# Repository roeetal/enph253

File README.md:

# enph253
## Robot competition

### Links
* Main source-code folder: https://github.com/roeetal/enph253/tree/master/Software/STM32/brain
* Google Slides for technical presentation: 
  https://docs.google.com/presentation/d/15P2V7RuZFssEo_z1w1n5baqb6ON2kBNIlDU9cCNbAWw/edit?usp=sharing
* Report / website:
https://axel-jacobsen.github.io/ENPHRobot/

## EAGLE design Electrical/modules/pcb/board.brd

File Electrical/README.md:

# Electrical

## Libraries

Create individual components that you cannot find or import from somewhere else.

## Design Blocks

Multiple compoenents connected together to form a single module, or design block. These get imported into the schematic.

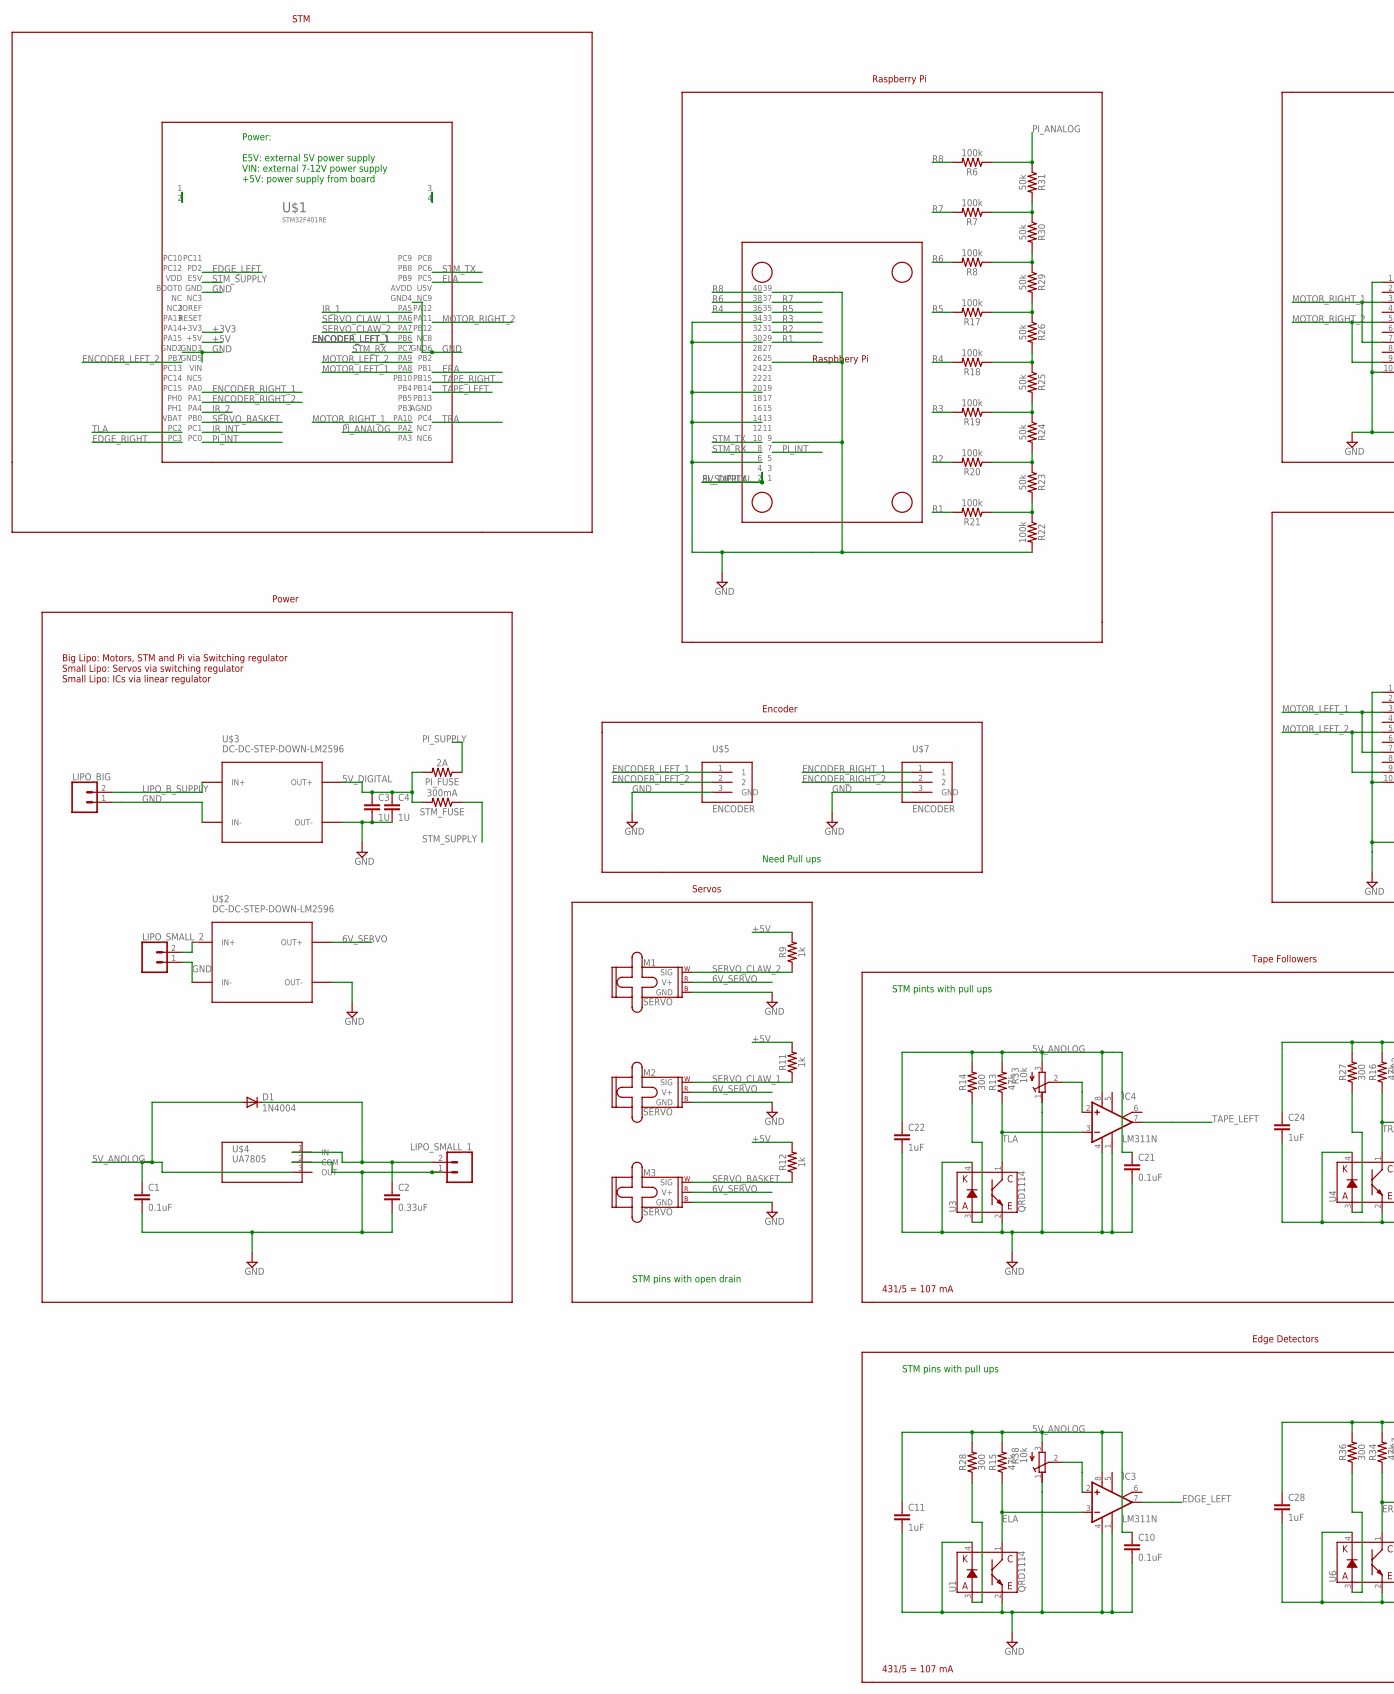
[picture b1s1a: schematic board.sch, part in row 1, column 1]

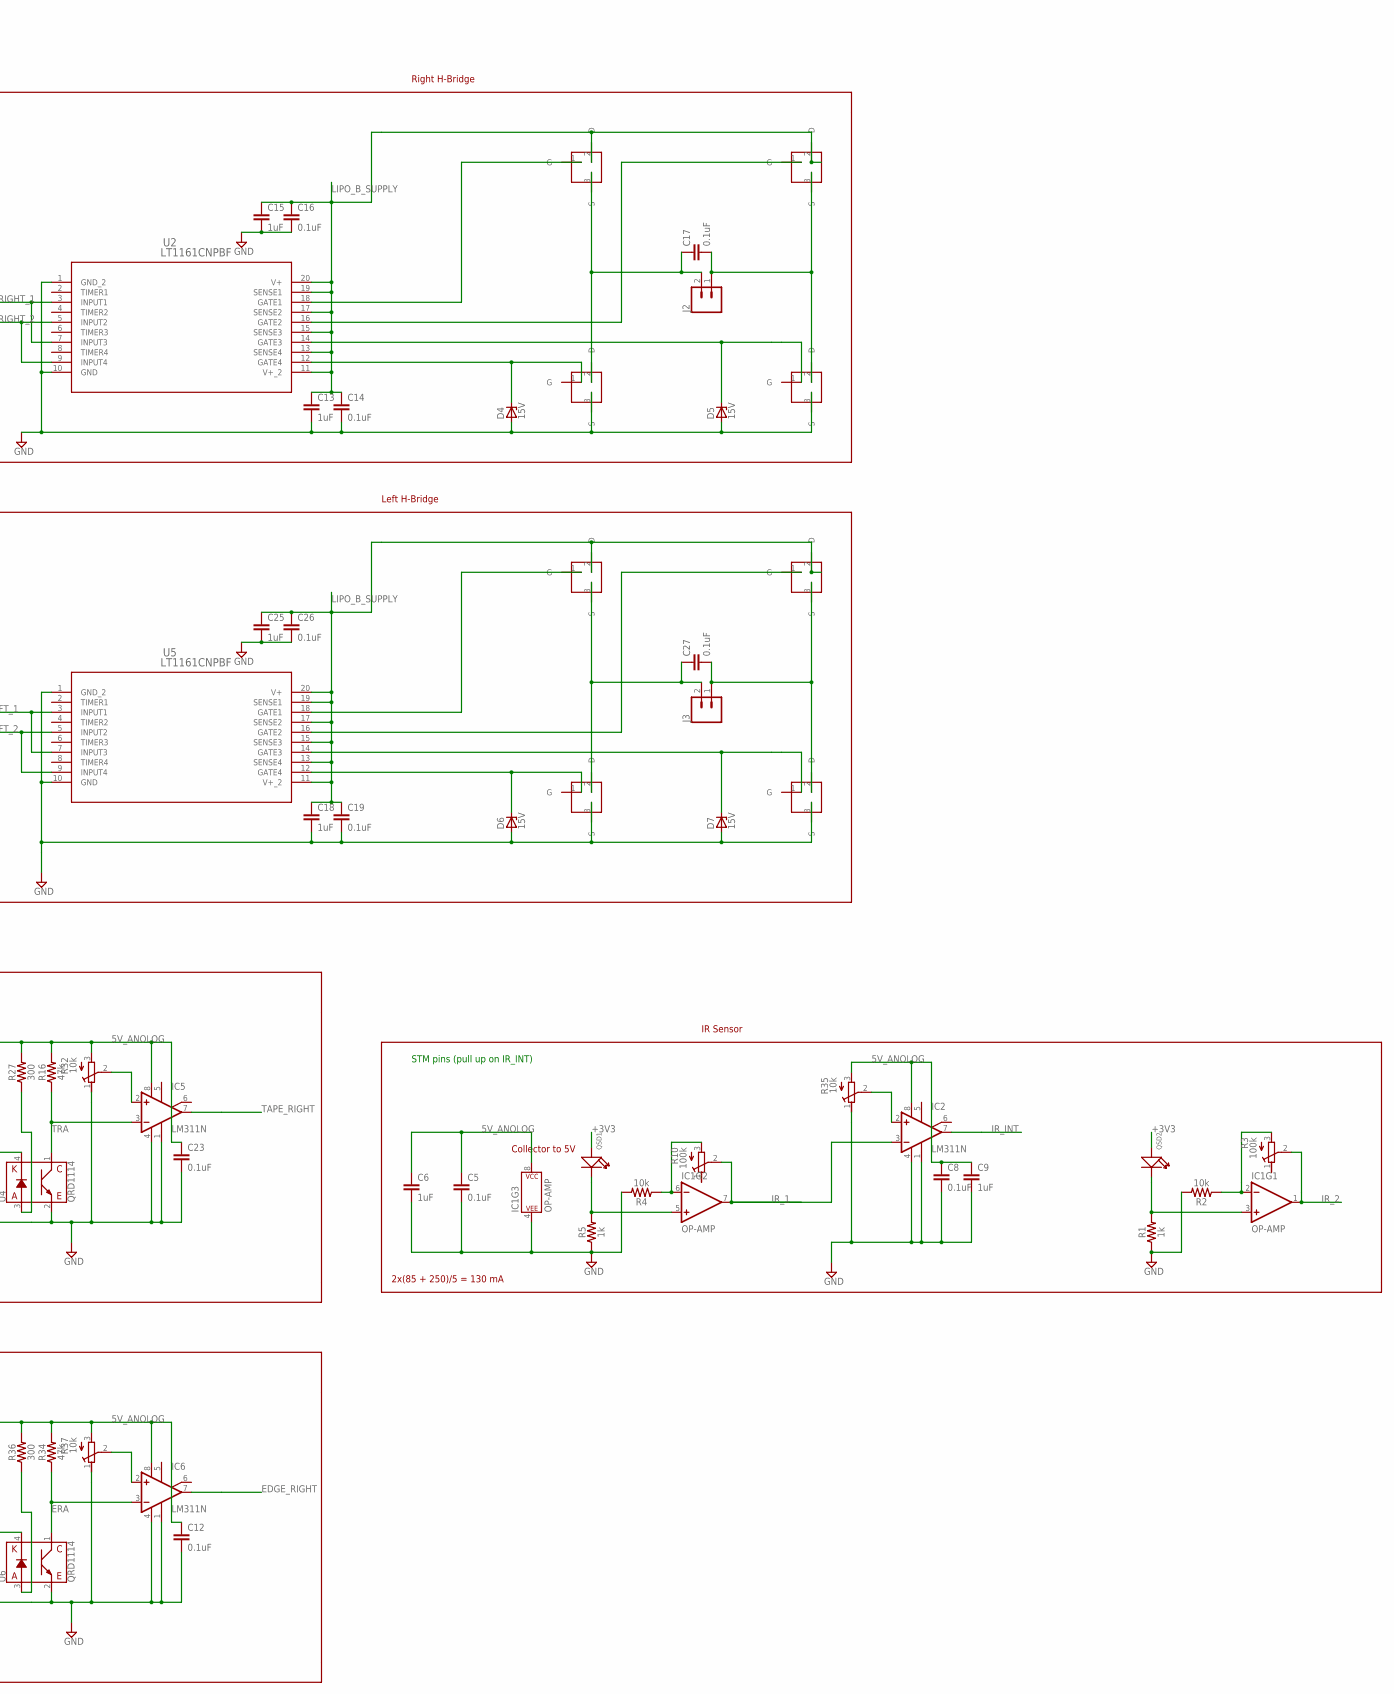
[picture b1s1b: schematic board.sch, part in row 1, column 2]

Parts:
C1, C5, C8, C10, C12, C14, C16, C17, C19, C21, C23, C26, C27: 0.1uF; CAP-PTH-SMALL-KIT
C2: 0.33uF; CAP-PTH-SMALL-KIT
C3, C4: 1U; C5B5
C6, C9, C11, C13, C15, C18, C22, C24, C25, C28: 1uF; CAP-PTH-SMALL-KIT
D1: 1N4004; DO41-10
D4, D5, D6, D7: 15V; DO41Z10
IC1: OP-AMP; DIP08
IC2, IC3, IC4, IC5, IC6: LM311N; DIL08
J2, J3: CONN_02; 1X02
LIPO_BIG: CONN_02; 1X02
LIPO_SMALL_1, LIPO_SMALL_2: CONN_02; 1X02
M1, M2, M3: SERVO; 1X03
PI_FUSE: 2A; AXIAL-0.3
QSD1, QSD2: DIP-LED-GREEN-GREEN(2P-D5MM); LED2-2.54-D5.0MM
R1, R5, R9, R11, R12: 1k; AXIAL-0.3
R2, R4: 10k; AXIAL-0.3
R3, R10: 100k; RTRIMT93YA
R6, R7, R8, R17, R18, R19, R20, R21, R22: 100k; AXIAL-0.3
R13, R15, R16, R34: 47k; AXIAL-0.3
R14, R27, R28, R36: 300; AXIAL-0.3
R23, R24, R25, R26, R29, R30, R31: 50k; AXIAL-0.3
R32, R33, R35, R37, R38: 10k; RTRIMT93YA
STM_FUSE: 300mA; AXIAL-0.3
U1, U3, U4, U6: QRD1114
U2, U5: LT1161CNPBF; PDIP-20_N
U$1: STM32F401RE; STM32
U$2, U$3: DC-DC-STEP-DOWN-LM2596
U$4: UA7805; TO-220AB
U$5, U$7: ENCODER; TO-220AB
U$6: RPI3; PI
U$11, U$12, U$13, U$14, U$15, U$16, U$17, U$18: HUF75321; TO-220AB

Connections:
5V_ANOLOG: C1.1, C5.1, C6.1, C8.1, C9.1, C10.1, C11.1, C12.1, C21.1, C22.1, C23.1, C24.1, C28.1, D1.A, IC1.8 (P$V+), IC2.8 (V+), IC3.8 (V+), IC4.8 (V+), IC5.8 (V+), IC6.8 (V+), R13.P$2 (2), R14.P$2 (2), R15.P$2 (2), R16.P$2 (2), R27.P$2 (2), R28.P$2 (2), R32.3 (A), R33.3 (A), R34.P$2 (2), R35.3 (A), R36.P$2 (2), R37.3 (A), R38.3 (A), U$4.3 (OUT)
6V_SERVO: M1.2 (V+), M2.2 (V+), M3.2 (V+), U$2.OUT+
+3V3: QSD1.+, QSD2.+, U$1.+3V3
+5V: R9.P$2 (2), R11.P$2 (2), R12.P$2 (2), U$1.+5V
EDGE_LEFT: IC3.7 (OUT), U$1.PD2
EDGE_RIGHT: IC6.7 (OUT), U$1.PC3
ELA: IC3.3 (-IN), R15.P$1 (1), U1.1 (C), U$1.PC5
ENCODER_LEFT_1: U$1.PB6, U$5.1
ENCODER_LEFT_2: U$1.PB7, U$5.2
ENCODER_RIGHT_1: U$1.PA0, U$7.1
ENCODER_RIGHT_2: U$1.PA1, U$7.2
ERA: IC6.3 (-IN), R34.P$1 (1), U6.1 (C), U$1.PB1
GND: C1.2, C2.2, C3.2, C4.2, C5.2, C6.2, C8.2, C9.2, C10.2, C11.2, C12.2, C13.2, C14.2, C15.2, C16.2, C18.2, C19.2, C21.2, C22.2, C23.2, C24.2, C25.2, C26.2, C28.2, D4.A, D5.A, D6.A, D7.A, IC1.4 (P$V-), IC2.1 (GND), IC2.4 (V-), IC3.1 (GND), IC3.4 (V-), IC4.1 (GND), IC4.4 (V-), IC5.1 (GND), IC5.4 (V-), IC6.1 (GND), IC6.4 (V-), LIPO_BIG.1, LIPO_SMALL_1.1, LIPO_SMALL_2.1, M1.3 (GND), M2.3 (GND), M3.3 (GND), R1.P$1 (1), R2.P$2 (2), R4.P$2 (2), R5.P$1 (1), R22.P$2 (2), R32.1 (E), R33.1 (E), R35.1 (E), R37.1 (E), R38.1 (E), U1.2 (E), U1.4 (K), U2.1 (GND_2), U2.10 (GND), U3.2 (E), U3.4 (K), U4.2 (E), U4.4 (K), U5.1 (GND_2), U5.10 (GND), U6.2 (E), U6.4 (K), U$1.GND, U$1.GND2, U$1.GND3, U$1.GND4, U$1.GND5, U$1.GND6, U$2.IN-, U$2.OUT-, U$3.IN-, U$3.OUT-, U$4.2 (COM), U$5.3 (GND), U$6.6, U$6.9, U$6.14, U$6.20, U$6.25, U$6.30, U$6.34, U$6.39, U$7.3 (GND), U$13.3 (S), U$14.3 (S), U$17.3 (S), U$18.3 (S)
IR_1: IC1.7 (OUT), IC2.3 (-IN), R10.2 (S), U$1.PA5
IR_2: IC1.1 (OUT), R3.2 (S), U$1.PA4
IR_INT: IC2.7 (OUT), U$1.PC1
LIPO_B_SUPPLY: C13.1, C14.1, C15.1, C16.1, C18.1, C19.1, C25.1, C26.1, LIPO_BIG.2, U2.11 (V+_2), U2.13 (SENSE4), U2.15 (SENSE3), U2.17 (SENSE2), U2.19 (SENSE1), U2.20 (V+), U5.11 (V+_2), U5.13 (SENSE4), U5.15 (SENSE3), U5.17 (SENSE2), U5.19 (SENSE1), U5.20 (V+), U$3.IN+, U$11.2 (D), U$12.2 (D), U$15.2 (D), U$16.2 (D)
MOTOR_LEFT_1: U5.3 (INPUT1), U5.7 (INPUT3), U$1.PA8
MOTOR_LEFT_2: U5.5 (INPUT2), U5.9 (INPUT4), U$1.PA9
MOTOR_RIGHT_1: U2.3 (INPUT1), U2.7 (INPUT3), U$1.PA10
MOTOR_RIGHT_2: U2.5 (INPUT2), U2.9 (INPUT4), U$1.PA11
unnamed: LIPO_SMALL_2.2, U$2.IN+
unnamed: IC1.2 (-IN), R2.P$1 (1), R3.3 (A)
unnamed: R28.P$1 (1), U1.3 (A)
unnamed: IC1.6 (-IN), R4.P$1 (1), R10.3 (A)
unnamed: R21.P$1 (1), R22.P$1 (1), R23.P$2 (2)
unnamed: IC5.2 (+IN), R32.2 (S)
unnamed: R20.P$1 (1), R23.P$1 (1), R24.P$2 (2)
unnamed: R19.P$1 (1), R24.P$1 (1), R25.P$2 (2)
unnamed: R18.P$1 (1), R25.P$1 (1), R26.P$2 (2)
unnamed: R17.P$1 (1), R26.P$1 (1), R29.P$2 (2)
unnamed: R8.P$1 (1), R29.P$1 (1), R30.P$2 (2)
unnamed: R7.P$1 (1), R30.P$1 (1), R31.P$2 (2)
unnamed: IC2.2 (+IN), R35.2 (S)
unnamed: IC3.2 (+IN), R38.2 (S)
unnamed: R14.P$1 (1), U3.3 (A)
unnamed: R36.P$1 (1), U6.3 (A)
unnamed: IC6.2 (+IN), R37.2 (S)
unnamed: U2.18 (GATE1), U$11.1 (G)
unnamed: U2.16 (GATE2), U$12.1 (G)
unnamed: D5.C, U2.14 (GATE3), U$14.1 (G)
unnamed: D4.C, U2.12 (GATE4), U$13.1 (G)
unnamed: C17.2, J2.1, U$12.3 (S), U$14.2 (D)
unnamed: C17.1, J2.2, U$11.3 (S), U$13.2 (D)
unnamed: U5.18 (GATE1), U$15.1 (G)
unnamed: U5.16 (GATE2), U$16.1 (G)
unnamed: IC4.2 (+IN), R33.2 (S)
unnamed: R27.P$1 (1), U4.3 (A)
unnamed: U$1.1, U$1.2
unnamed: D7.C, U5.14 (GATE3), U$18.1 (G)
unnamed: D6.C, U5.12 (GATE4), U$17.1 (G)
unnamed: C27.2, J3.1, U$16.3 (S), U$18.2 (D)
unnamed: C27.1, J3.2, U$15.3 (S), U$17.2 (D)
unnamed: U$1.3, U$1.4
OUTPUT1: IC1.5 (+IN), QSD1.-, R5.P$2 (2)
OUTPUT2: IC1.3 (+IN), QSD2.-, R1.P$2 (2)
PI_ANALOG: R6.P$1 (1), R31.P$1 (1), U$1.PA2
PI_INT: U$1.PC0, U$6.7
R1: R21.P$2 (2), U$6.29
R2: R20.P$2 (2), U$6.31
R3: R19.P$2 (2), U$6.33
R4: R18.P$2 (2), U$6.36
R5: R17.P$2 (2), U$6.35
R6: R8.P$2 (2), U$6.38
R7: R7.P$2 (2), U$6.37
R8: R6.P$2 (2), U$6.40
SERVO_BASKET: M3.1 (SIG), R12.P$1 (1), U$1.PB0
SERVO_CLAW_1: M2.1 (SIG), R11.P$1 (1), U$1.PA6
SERVO_CLAW_2: M1.1 (SIG), R9.P$1 (1), U$1.PA7
STM_RX: U$1.PC7, U$6.8
STM_SUPPLY: STM_FUSE.P$1 (1), U$1.E5V
STM_TX: U$1.PC6, U$6.10
TAPE_LEFT: IC4.7 (OUT), U$1.PB14
TAPE_RIGHT: IC5.7 (OUT), U$1.PB15
TLA: IC4.3 (-IN), R13.P$1 (1), U3.1 (C), U$1.PC2
TRA: IC5.3 (-IN), R16.P$1 (1), U4.1 (C), U$1.PC4
V_IN1: C2.1, D1.C, LIPO_SMALL_1.2, U$4.1 (IN)

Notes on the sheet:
Power: E5V: external 5V power supply VIN: external 7-12V power supply +5V: power supply from board
Collector to 5V
STM pins (pull up on IR_INT)
STM pints with pull ups
Tape Followers
IR Sensor
2x(85 + 250)/5 = 130 mA
431/5 = 107 mA
Big Lipo: Motors, STM and Pi via Switching regulator Small Lipo: Servos via switching regulator Small Lipo: ICs via linear regulator
Power
STM
Servos
STM pins with open drain
Left H-Bridge
Right H-Bridge
Encoder
Raspberry Pi
STM pins with pull ups
Edge Detectors
Need Pull ups

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
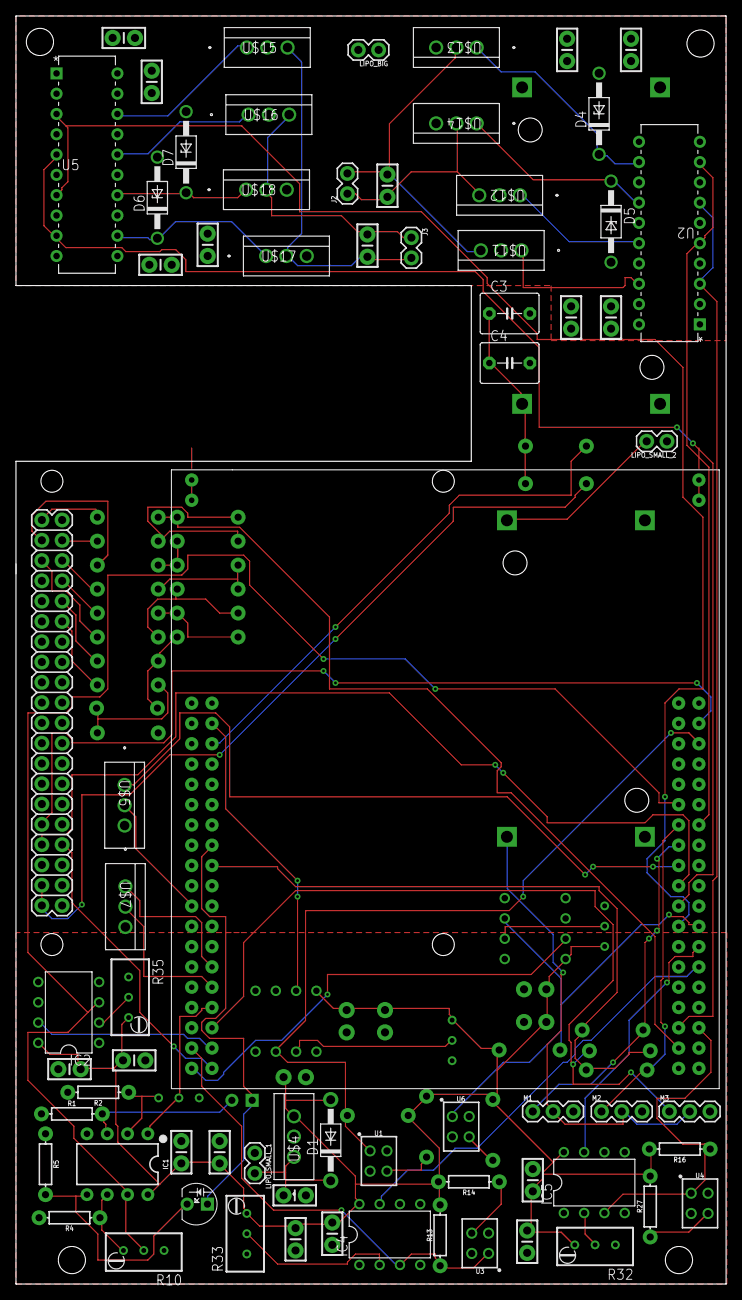
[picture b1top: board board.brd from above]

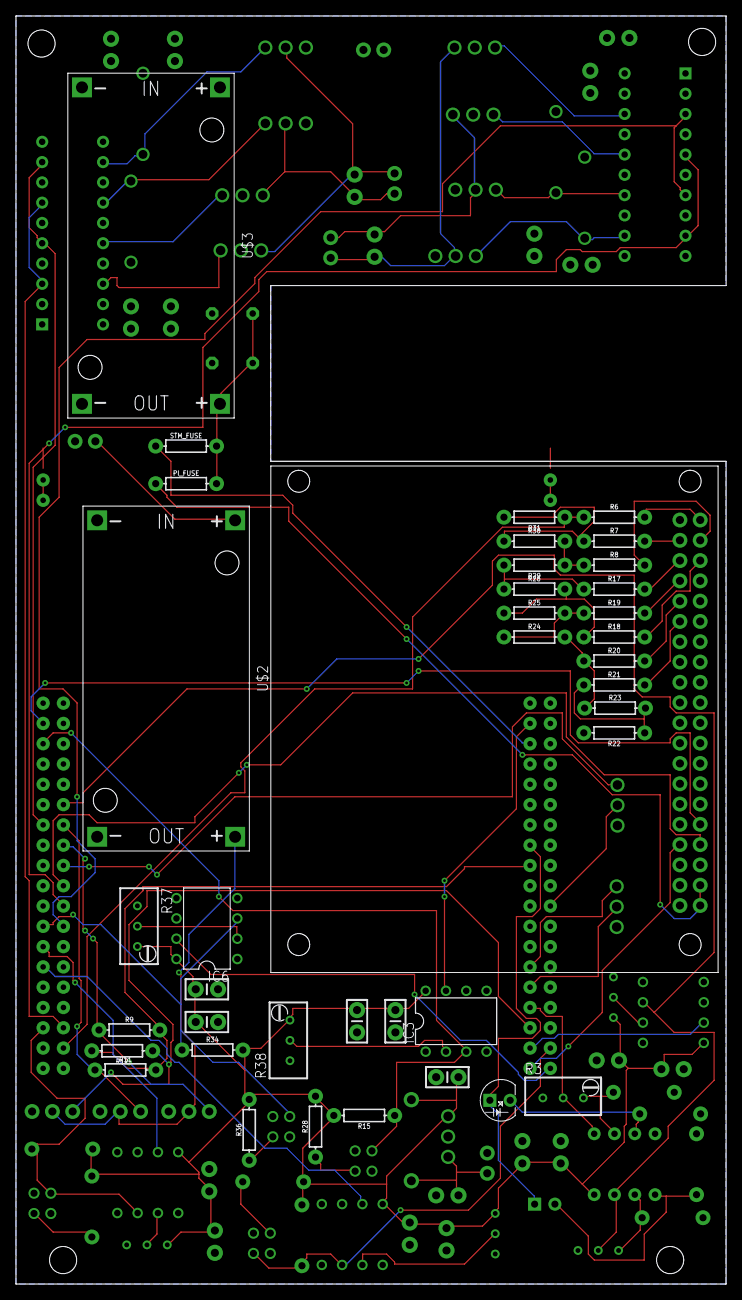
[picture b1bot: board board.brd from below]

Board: 2 copper layers, 88.9 x 158.8 mm, 108 parts (38 on the bottom side), 79 nets.

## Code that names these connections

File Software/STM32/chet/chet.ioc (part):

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Mcu.Name=STM32F103C(8-B)Tx
Mcu.Package=LQFP48
Mcu.UserName=STM32F103C8Tx
PA0-WKUP.GPIOParameters=GPIO_Label
PA0-WKUP.GPIO_Label=IR_1
PA0-WKUP.Signal=ADCx_IN0
PA1.GPIOParameters=GPIO_Label
PA1.GPIO_Label=IR_2
PA1.Signal=ADCx_IN1
PA10.GPIOParameters=GPIO_Speed,GPIO_Label
PA10.GPIO_Label=MOTOR_R_F
PA10.GPIO_Speed=GPIO_SPEED_FREQ_HIGH
PA10.Signal=S_TIM1_CH3
PA11.GPIOParameters=GPIO_Speed,GPIO_Label
PA11.GPIO_Label=MOTOR_R_B
PA11.GPIO_Speed=GPIO_SPEED_FREQ_HIGH
PA11.Signal=S_TIM1_CH4
PA12.GPIOParameters=GPIO_Label
PA12.GPIO_Label=QRD_INT
PA12.Signal=GPXTI12
PA13.GPIOParameters=GPIO_PuPd,GPIO_Label
PA13.GPIO_Label=MENU
PA13.GPIO_PuPd=GPIO_PULLUP
PA13.Signal=GPIO_Input
PA15.GPIOParameters=GPIO_ModeDefaultPP,GPIO_Speed,GPIO_Label
PA15.GPIO_Label=SERVO_BASKET
PA15.GPIO_ModeDefaultPP=GPIO_MODE_AF_OD
PA15.GPIO_Speed=GPIO_SPEED_FREQ_HIGH
PA15.Signal=S_TIM2_CH1_ETR
PA2.GPIOParameters=GPIO_Label
PA2.GPIO_Label=STM_TX
PA2.Mode=Asynchronous
PA2.Signal=USART2_TX
PA3.GPIOParameters=GPIO_Label
PA3.GPIO_Label=STM_RX
PA3.Mode=Asynchronous
PA3.Signal=USART2_RX
PA4.GPIOParameters=GPIO_Label
PA4.GPIO_Label=PI_ANALOG
PA4.Signal=ADCx_IN4
PA5.GPIOParameters=GPIO_Label
PA5.GPIO_Label=EL
PA5.Signal=ADCx_IN5
PA6.GPIOParameters=GPIO_Label
PA6.GPIO_Label=ER
PA6.Signal=ADCx_IN6
PA7.GPIOParameters=GPIO_Label
PA7.GPIO_Label=TL
PA7.Signal=ADCx_IN7
PA8.GPIOParameters=GPIO_Speed,GPIO_Label
PA8.GPIO_Label=MOTOR_L_F
PA8.GPIO_Speed=GPIO_SPEED_FREQ_HIGH
PA8.Signal=S_TIM1_CH1
PA9.GPIOParameters=GPIO_Speed,GPIO_Label
PA9.GPIO_Label=MOTOR_L_B
PA9.GPIO_Speed=GPIO_SPEED_FREQ_HIGH
PA9.Signal=S_TIM1_CH2
PB0.GPIOParameters=GPIO_Label
PB0.GPIO_Label=TR
PB0.Signal=ADCx_IN8
PB1.GPIOParameters=GPIO_Label
PB1.GPIO_Label=PI_INT
PB1.Signal=GPXTI1
PB10.GPIOParameters=GPIO_ModeDefaultPP,GPIO_Speed,GPIO_Label
PB10.GPIO_Label=SERVO_CLAW_ARM
PB10.GPIO_ModeDefaultPP=GPIO_MODE_AF_OD
PB10.GPIO_Speed=GPIO_SPEED_FREQ_HIGH
PB10.Signal=S_TIM2_CH3
PB12.GPIOParameters=GPIO_Label
PB12.GPIO_Label=EDGE_RIGHT
PB12.Signal=GPIO_Input
PB13.GPIOParameters=GPIO_Label
PB13.GPIO_Label=EDGE_LEFT
PB13.Signal=GPIO_Input
PB14.GPIOParameters=GPIO_Label
PB14.GPIO_Label=TAPE_RIGHT
PB14.Signal=GPIO_Input
PB15.GPIOParameters=GPIO_Label
PB15.GPIO_Label=TAPE_LEFT
PB15.Signal=GPIO_Input
PB2.GPIOParameters=GPIO_PuPd,GPIO_Label
PB2.GPIO_Label=IR_INT
PB2.GPIO_PuPd=GPIO_PULLUP
PB2.Signal=GPXTI2
PB3.GPIOParameters=GPIO_ModeDefaultPP,GPIO_Speed,GPIO_Label
PB3.GPIO_Label=SERVO_CLAW_JAW
PB3.GPIO_ModeDefaultPP=GPIO_MODE_AF_OD
PB3.GPIO_Speed=GPIO_SPEED_FREQ_HIGH
PB3.Signal=S_TIM2_CH2
PB4.GPIOParameters=GPIO_PuPd,GPIO_Label
PB4.GPIO_Label=ENCODER_LEFT_1
PB4.GPIO_PuPd=GPIO_PULLUP
PB4.Signal=S_TIM3_CH1
PB5.GPIOParameters=GPIO_PuPd,GPIO_Label
PB5.GPIO_Label=ENCODER_LEFT_2
PB5.GPIO_PuPd=GPIO_PULLUP
PB5.Signal=S_TIM3_CH2
PB6.GPIOParameters=GPIO_PuPd,GPIO_Label
PB6.GPIO_Label=ENCODER_RIGHT_1
PB6.GPIO_PuPd=GPIO_PULLUP
PB6.Signal=S_TIM4_CH1
PB7.GPIOParameters=GPIO_PuPd,GPIO_Label
PB7.GPIO_Label=ENCODER_RIGHT_2
PB7.GPIO_PuPd=GPIO_PULLUP
PB7.Signal=S_TIM4_CH2
PB8.Mode=I2C
PB8.Signal=I2C1_SCL
PB9.Mode=I2C
PB9.Signal=I2C1_SDA
RCC.SYSCLKFreq_VALUE=64000000
RCC.SYSCLKSource=RCC_SYSCLKSOURCE_PLLCLK
board=custom

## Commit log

2018-05-25 init
2018-05-25 add TINAH frequency measuring software
2018-05-28 Added control_loop.xml
2018-05-28 Just some ideas about how the software can be structured.
2018-05-28 tape follower init
2018-05-29 init elec
2018-05-29 elec init
2018-06-01 lab2
2018-06-01 peak detection
2018-06-04 parts
2018-06-05 edge detection
2018-06-05 nothing new
2018-06-08 hbridge
2018-06-09 code for high frequency detection
2018-06-09 freq
2018-06-11 Added code for opencv ewok spotting
2018-06-11 Added photos and videos for training. Started detection algorithm
2018-06-15 matlab edge detection start
2018-06-16 update ignore file
2018-06-16 tape follow update with PID
2018-06-16 pressy start
2018-06-18 Update pressy.md
    Made some suggestions, what you guys think. I think its a more fluid, understandable approach to presenting.
2018-06-18 Added block diagram
2018-06-18 Block Diagrams
2018-06-19 update block diagram
2018-06-19 Delete old block diag
    - view new diagram xml files on draw.io
2018-06-19 Added code for basic object detection network; Removed old color filter methods
2018-06-20 block diagram update
2018-06-20 another one
2018-06-20 Software Flowcharts Complete
2018-06-20 stm32
2018-06-20 make stizzle
2018-06-22 oled example
2018-06-22 Presentation (#2)
    * pressy start
    * Update pressy.md
    Made some suggestions, what you guys think. I think its a more fluid, understandable approach to presenting.
    * Added block diagram
    * Delete Untitled Diagram.png
    * Block Diagrams
2018-06-22 Edges (#4)
    * matlab edge detection start
    * updates
    * stm32
    * make stizzle
2018-06-22 Added calculations spreadsheet
2018-06-22 Added frame rate test code
2018-06-22 oled update
2018-06-22 Create Generic STM setup
2018-06-22 jokes, EWARM is not as good as make
2018-06-23 pwm works, same duty cycle though
2018-06-23 move furhter down stm read
2018-06-23 Added PID library
2018-06-23 quick push for apple store
2018-06-23 add ADC pin
2018-06-24 Implemented PID; Derivative term needs work
2018-06-25 Removed useless print statement
2018-06-29 Added training images to gitignore
2018-06-29 forgot a folder
2018-06-29 Added script to pull training images from video files
2018-06-29 continuous ADC Sampling complete
2018-06-29 first attemp - unsuccessful
2018-06-29 works
2018-06-30 ir square wave schematic
2018-06-30 test pwm
2018-06-30 regulator
2018-06-30 Revert "regulator"
    This reverts commit 0ff39721ac493a19ae8de3e9ca2d5f687df9d53b.
2018-07-01 started pcb
2018-07-01 pcbs
2018-07-02 done, not clean. will clean when we integrate
2018-07-02 readme encoder
2018-07-04 Sonar Working
2018-07-04 Added wrapper script to get error and output to GPIO
2018-07-04 Update Sonar Jazz
2018-07-04 fix readme
2018-07-04 Added comments
2018-07-04 functional wiskers
2018-07-04 add little readme, lower ADC bits
2018-07-04 circuit updates
2018-07-05 ir sensor code works and module tuned
2018-07-05 Servo done
2018-07-05 serrrrrvoooowwww
2018-07-05 Moved GPIO setup to separate function
2018-07-05 Added debug mode to DAC_output; Forced length of binary array to be 8
2018-07-05 servo done - make libraries pretty
2018-07-05 hbridge pcb done
2018-07-06 done
2018-07-07 Added DS_Store to gitignore
2018-07-07 Added bridge stuff
2018-07-08 almost there
2018-07-08 Added neural network and demo function with video argument
2018-07-09 Replaced python things with c things. Makes sense given branch name
2018-07-09 finalized circuit
2018-07-09 Added libraries for picamera, GPIO
2018-07-10 renamed folder
2018-07-10 Started new makefile
2018-07-10 Added .DS_Store to gitignore
2018-07-10 Added training videos and 2 approaches to edge detection
2018-07-11 add lst files to gitignore
2018-07-11 remove false ir files
2018-07-11 fixed gitignore
2018-07-11 Actually fixed the gitignore this time
2018-07-11 Edge detection progress
2018-07-11 menu with encoder, push and motor control
2018-07-11 upadtes
2018-07-11 Updated edge detection
2018-07-11 Added more non-ewok images; Combined edge detection and ewok network into one file
2018-07-12 tape follower almost there
2018-07-12 tape
2018-07-12 tape follower
2018-07-13 motor control
2018-07-13 Added project to test camera
2018-07-13 Maked it
2018-07-13 Updated Makefile
2018-07-13 encoder
2018-07-13 tape following and some encoder
2018-07-14 tape follower init motor speed
2018-07-17 Lots of changes to make files; built lots of things; it works now don't touch
2018-07-17 encoders done
2018-07-17 encoder finished
2018-07-17 encoder done
2018-07-17 Trained on ewoks
2018-07-17 adc dma works
2018-07-17 update cube + cleanup
2018-07-17 ir works
2018-07-17 integrated freq
2018-07-17 frequency detection integrated
2018-07-18 mysterm
2018-07-18 IR integrated. Cleaned up.
2018-07-18 frequency works
2018-07-18 updates to cube
2018-07-18 clean, working, updated
2018-07-19 servo basket integration
2018-07-19 updated cube, pcb
2018-07-20 fixes
2018-07-20 pi nav integration
2018-07-20 pi nav
2018-07-20 mech
2018-07-24 blue pill project
2018-07-24 import claw.h shes done boys
2018-07-24 encoder, button, screen works on blue pill
2018-07-24 frequency also works
2018-07-24 pi navigation done
2018-07-25 working
2018-07-25 integrated
2018-07-25 pi navving
2018-07-26 claw interrupt
2018-07-26 add claw code
2018-07-27 haha
2018-07-27 lalala
2018-07-27 it works a tricksy fools
2018-07-27 test
2018-07-27 shit works and ready
2018-07-31 testing encoder pid
2018-07-31 turning
2018-07-31 navving
2018-07-31 go straight
2018-07-31 turning fixed i think,
2018-07-31 update f4 cube
2018-07-31 ported over to f4
2018-07-31 continued
2018-07-31 alarm working
2018-08-01 edge detection works
2018-08-01 claw working
2018-08-01 edge, tape done
2018-08-01 everything works
2018-08-01 merged
2018-08-02 save
2018-08-02 some updates
2018-08-02 push
2018-08-03 checkpoit before changin adc
2018-08-03 shits fucked
2018-08-03 remove adc channel 2/3
2018-08-03 ioc is toight
2018-08-05 encoder pid
2018-08-06 recubed
2018-08-06 test tests
2018-08-06 create tests and create project to reset PWM pins
2018-08-07 running robot
2018-08-07 temp
2018-08-07 course coded
2018-08-08 full course untested
2018-08-09 Removed interrupts. Navigates to 1st ewok
2018-08-09 save plz
2018-08-09 if there is a god this code will work please
2018-08-09 6am push
2018-08-09 last push
2018-08-10 done course
2018-08-10 Side hoe (#26)
    * update f4 cube
    * ported over to f4
    * continued
    * alarm working
    * edge detection works
    * f

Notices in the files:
parts and their libraries:
SparkFun-Capacitors: Licensing: Creative Commons ShareAlike 4.0 International - https://creativecommons.org/licenses/by-sa/4.0
diy-modules: Released under the Creative Commons Attribution 4.0 International License: http://creativecommons.org/licenses/by/4.0
